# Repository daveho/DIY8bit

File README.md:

# DIY 8-bit computer video series

This repository has files and resources for the DIY 8-bit computer video series I am working on.

My youtube channel: <https://www.youtube.com/@davehohacks>

DIY 8-bit computer playlist: <https://www.youtube.com/playlist?list=PL9zJKV-F2eMyKY6qdesRQP_mAhBCMSw2T>

Some episodes have a specific subdirectory, e.g., `Episode02` for episode 2.

Feedback is welcome: <mailto:david.hovemeyer@gmail.com>.

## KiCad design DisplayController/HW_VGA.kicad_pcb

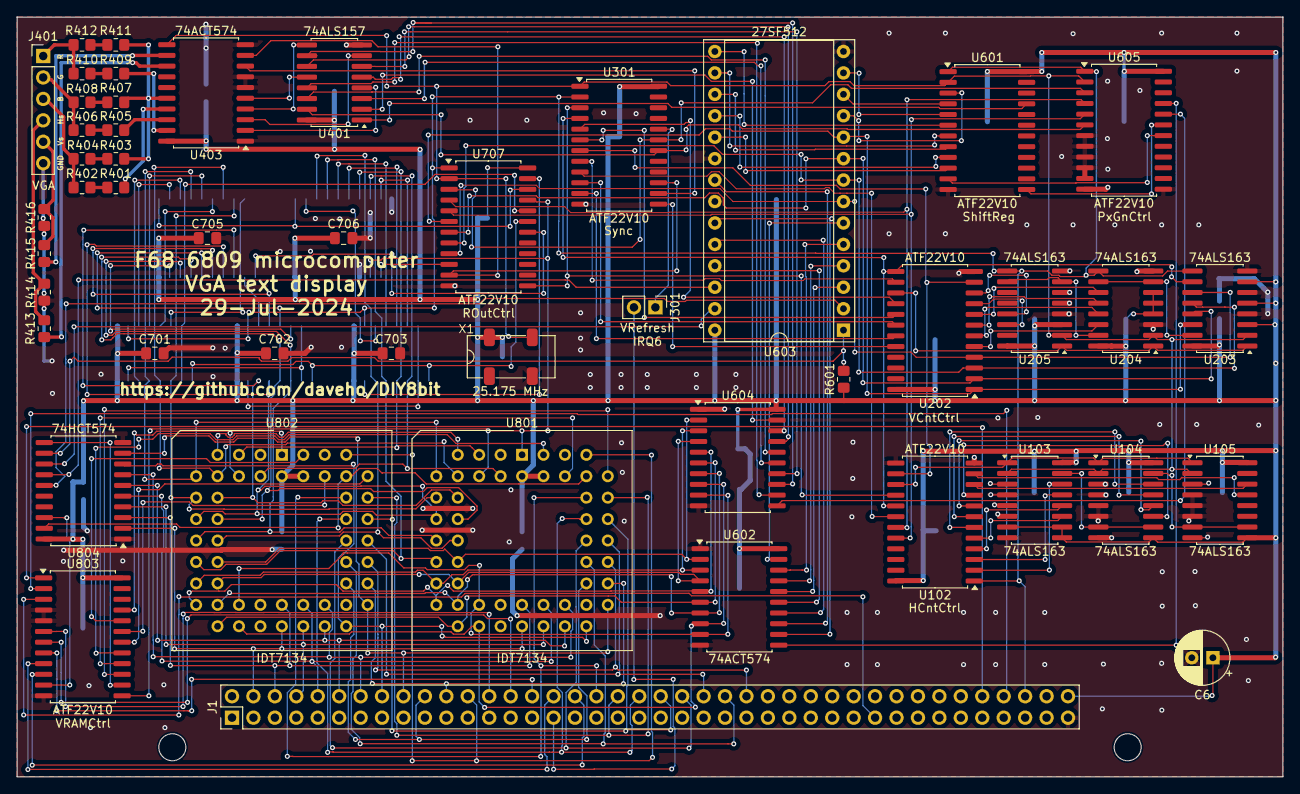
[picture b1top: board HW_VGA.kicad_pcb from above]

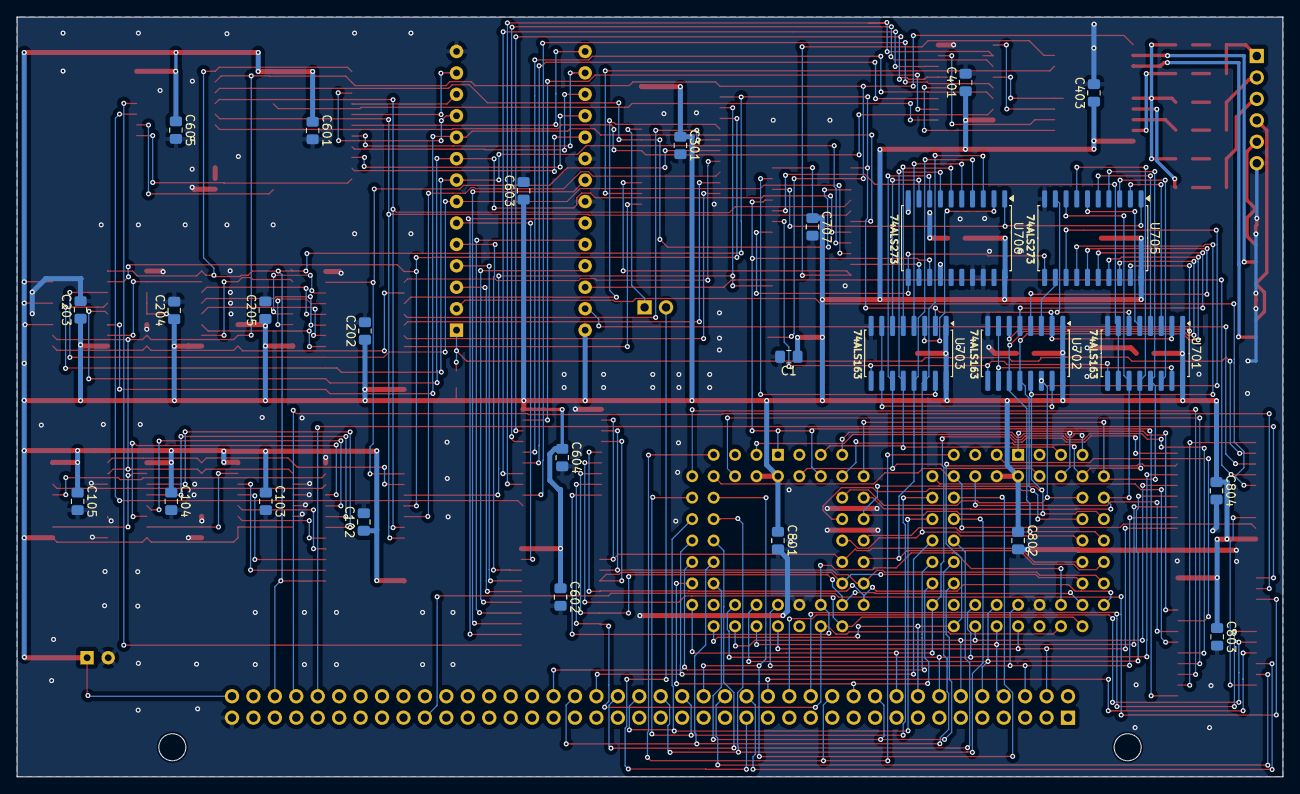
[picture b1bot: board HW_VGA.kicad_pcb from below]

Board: 2 copper layers, 150.0 x 90.0 mm, 75 parts (27 on the bottom side), 181 nets.

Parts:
C1, C102, C103, C104, C105, C202, C203, C204, C205, C301, C401, C403, C601, C602, C603, C604, C605, C701, C702, C703, C705, C706, C707, C801, C802, C803, C804: 100 nF; C_0805_2012Metric_Pad1.18x1.45mm_HandSolder
C6: 22μF; CP_Radial_D6.3mm_P2.50mm
J1: Conn_02x40_Odd_Even; PinHeader_2x40_P2.54mm_Vertical
J301: Conn_01x02; PinHeader_1x02_P2.54mm_Vertical
J401: Conn_01x06; PinHeader_1x06_P2.54mm_Vertical
R401, R405, R409: 620; R_0805_2012Metric_Pad1.20x1.40mm_HandSolder
R402, R406, R410: 75; R_0805_2012Metric_Pad1.20x1.40mm_HandSolder
R403, R407, R411: 1K; R_0805_2012Metric_Pad1.20x1.40mm_HandSolder
R404, R408, R412: 390; R_0805_2012Metric_Pad1.20x1.40mm_HandSolder
R413, R415: 2K; R_0805_2012Metric_Pad1.20x1.40mm_HandSolder
R414, R416: 3K; R_0805_2012Metric_Pad1.20x1.40mm_HandSolder
R601: 4k7; R_0805_2012Metric_Pad1.20x1.40mm_HandSolder
U102, U202, U301, U601, U605, U707, U803: ATF22V10; SOIC-24W_7.5x15.4mm_P1.27mm
U103, U104, U105, U203, U204, U205, U701, U702, U703: 74ALS163; SOIC-16W_5.3x10.2mm_P1.27mm
U401: 74ALS157; SOIC-16W_5.3x10.2mm_P1.27mm
U403, U602, U604: 74ACT574; SOIC-20W_7.5x12.8mm_P1.27mm
U603: 27SF512; DIP-28_W15.24mm_Socket
U705, U706: 74ALS273; SOIC-20W_7.5x12.8mm_P1.27mm
U801, U802: IDT7134; PLCC-52_THT-Socket
U804: 74HCT574; SOIC-20W_7.5x12.8mm_P1.27mm
X1: 25.175 MHz; SG-636P

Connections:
/-HostRMEM: J1.72, U803.1 (I0/CLK)
/-HostWMEM: J1.74, U803.2 (I1)
/-RST: J1.76, U102.1 (I0/CLK), U203.9 (~PE), U204.9 (~PE), U205.9 (~PE), U301.2 (I1), U601.1 (I0/CLK), U605.1 (I0/CLK), U701.2 (CP), U702.2 (CP), U703.2 (CP), U707.1 (I0/CLK)
/-VIS: U301.18 (I/O16), U401.15 (E), U605.6 (I5)
/BGBlue: U401.11 (I0c), U604.17 (Q2)
/BGGreen: U401.5 (I0b), U604.18 (Q1)
/BGIntens: U401.14 (I0d), U604.16 (Q3)
/BGRed: U401.2 (I0a), U604.19 (Q0)
/CLK: U103.2 (CP), U104.2 (CP), U105.2 (CP), U203.2 (CP), U204.2 (CP), U205.2 (CP), U301.1 (I0/CLK), U403.11 (Cp), U601.2 (I1), U605.2 (I1), U707.2 (I1), X1.3 (OUT)
/FGBlue: U401.10 (I1c), U604.13 (Q6)
/FGGreen: U401.6 (I1b), U604.14 (Q5)
/FGIntens: U401.13 (I1d), U604.12 (Q7)
/FGRed: U401.3 (I1a), U604.15 (Q4)
/FontA12: U603.2 (A12), U804.15 (Q4)
/FontA13: U603.26 (A13), U804.14 (Q5)
/FontA14: U603.27 (A14), U804.13 (Q6)
/FontA15: R601.2, U603.1 (A15), U804.12 (Q7)
/HBeginActive: U102.19 (I/O17), U605.4 (I3), U707.4 (I3)
/HBeginPulse: U102.16 (I/O14), U301.3 (I2), U707.13 (I11)
/HCOUNT_END: U102.14 (I/O12), U202.11 (I10), U301.7 (I6)
/HCount/-HCOUNT_CLR: U102.15 (I/O13), U103.1 (~MR), U104.1 (~MR), U105.1 (~MR)
/HCount/HC0: U102.2 (I1), U103.14 (Q0)
/HCount/HC1: U102.3 (I2), U103.13 (Q1)
/HCount/HC2: U102.4 (I3), U103.12 (Q2)
/HCount/HC3: U102.5 (I4), U103.11 (Q3)
/HCount/HC4: U102.6 (I5), U104.14 (Q0)
/HCount/HC5: U102.7 (I6), U104.13 (Q1)
/HCount/HC6: U102.8 (I7), U104.12 (Q2)
/HCount/HC7: U102.9 (I8), U104.11 (Q3)
/HCount/HC8: U102.10 (I9), U105.14 (Q0)
/HCount/HC9: U102.11 (I10), U105.13 (Q1)
/HEndActive: U102.20 (I/O18), U605.5 (I4), U707.5 (I4)
/HEndPulse: U102.17 (I/O15), U202.13 (I11), U203.10 (CET), U301.4 (I3)
/HSync: U301.14 (I/O12), U403.8 (D6)
/HVisEnd: U102.18 (I/O16), U301.9 (I8)
/HostA0: J1.36, U801.45 (A0R), U802.45 (A0R)
/HostA1: J1.38, U801.44 (A1R), U802.44 (A1R)
/HostA2: J1.40, U801.43 (A2R), U802.43 (A2R)
/HostA3: J1.42, U801.42 (A3R), U802.42 (A3R)
/HostA4: J1.44, U801.41 (A4R), U802.41 (A4R)
/HostA5: J1.46, U801.40 (A5R), U802.40 (A5R)
/HostA6: J1.48, U801.39 (A6R), U802.39 (A6R)
/HostA7: J1.50, U801.38 (A7R), U802.38 (A7R)
/HostA8: J1.20, U801.37 (A8R), U802.37 (A8R)
/HostA9: J1.22, U801.36 (A9R), U802.36 (A9R)
/HostA10: J1.24, U801.47 (A10R), U802.47 (A10R)
/HostA11: J1.26, U803.6 (I5)
/HostA12: J1.28, U803.7 (I6)
/HostA13: J1.30, U803.8 (I7)
/HostA14: J1.32, U803.9 (I8)
/HostA15: J1.34, U803.10 (I9)
/HostD0: J1.4, U801.27 (IOR0), U802.27 (IOR0), U804.2 (D0)
/HostD1: J1.6, U801.28 (IOR1), U802.28 (IOR1), U804.3 (D1)
/HostD2: J1.8, U801.29 (IOR2), U802.29 (IOR2), U804.4 (D2)
/HostD3: J1.10, U801.30 (IOR3), U802.30 (IOR3), U804.5 (D3)
/HostD4: J1.12, U801.31 (IOR4), U802.31 (IOR4), U804.6 (D4)
/HostD5: J1.14, U801.32 (IOR5), U802.32 (IOR5), U804.7 (D5)
/HostD6: J1.16, U801.33 (IOR6), U802.33 (IOR6), U804.8 (D6)
/HostD7: J1.18, U801.34 (IOR7), U802.34 (IOR7), U804.9 (D7)
/IRQ6: J1.31, J301.2
/Output/Blue: R401.2, U403.17 (Q2)
/Output/Bout: J401.3, R402.1, R404.2
/Output/Gout: J401.2, R406.1, R408.2
/Output/Green: R405.2, U403.18 (Q1)
/Output/HSyncOut: J401.4, R413.2, R414.1
/Output/Intense: R403.1, R407.1, R411.1, U403.16 (Q3)
/Output/Red: R409.2, U403.19 (Q0)
/Output/Rout: J401.1, R410.1, R412.2
/Output/VSyncOut: J401.5, R415.2, R416.1
/Pixel: U401.1 (S), U601.21 (I/O19)
/Pixgen/-SRLoad: U601.11 (I10), U605.18 (I/O16)
/Pixgen/-SRShift: U601.13 (I11), U605.19 (I/O17)
/Pixgen/CD0: U601.3 (I2), U603.11 (D0)
/Pixgen/CD1: U601.4 (I3), U603.12 (D1)
/Pixgen/CD2: U601.5 (I4), U603.13 (D2)
/Pixgen/CD3: U601.6 (I5), U603.15 (D3)
/Pixgen/CD4: U601.7 (I6), U603.16 (D4)
/Pixgen/CD5: U601.8 (I7), U603.17 (D5)
/Pixgen/CD6: U601.9 (I8), U603.18 (D6)
/Pixgen/CD7: U601.10 (I9), U603.19 (D7)
/Pixgen/CRA4: U602.19 (Q0), U603.6 (A4)
/Pixgen/CRA5: U602.18 (Q1), U603.5 (A5)
/Pixgen/CRA6: U602.17 (Q2), U603.4 (A6)
/Pixgen/CRA7: U602.16 (Q3), U603.3 (A7)
/Pixgen/CRA8: U602.15 (Q4), U603.25 (A8)
/Pixgen/CRA9: U602.14 (Q5), U603.24 (A9)
/Pixgen/CRA10: U602.13 (Q6), U603.21 (A10)
/Pixgen/CRA11: U602.12 (Q7), U603.23 (A11)
/Pixgen/LoadAttrCP: U604.11 (Cp), U605.20 (I/O18)
/Pixgen/LoadCharCP: U602.11 (Cp), U605.21 (I/O19)
/Readout/-LoadReadoutAddr: U701.9 (~PE), U702.9 (~PE), U703.9 (~PE), U707.19 (I/O17)
/Readout/-RowBeginClear: U705.1 (~Mr), U706.1 (~Mr), U707.22 (I/O20)
/Readout/IncrReadoutAddr: U701.7 (CEP), U701.10 (CET), U707.20 (I/O18)
/Readout/ReadoutAddrTCnt: U703.15 (TC), U707.23 (I/O21)
/Readout/RowBeginA0: U701.3 (D0), U705.2 (Q0)
/Readout/RowBeginA1: U701.4 (D1), U705.5 (Q1)
/Readout/RowBeginA2: U701.5 (D2), U705.6 (Q2)
/Readout/RowBeginA3: U701.6 (D3), U705.9 (Q3)
/Readout/RowBeginA4: U702.3 (D0), U705.12 (Q4)
/Readout/RowBeginA5: U702.4 (D1), U705.15 (Q5)
/Readout/RowBeginA6: U702.5 (D2), U705.16 (Q6)
/Readout/RowBeginA7: U702.6 (D3), U705.19 (Q7)
/Readout/RowBeginA8: U703.3 (D0), U706.2 (Q0)
/Readout/RowBeginA9: U703.4 (D1), U706.5 (Q1)
/Readout/RowBeginA10: U703.5 (D2), U706.6 (Q2)
/Readout/RowBeginA11: U703.6 (D3), U706.9 (Q3)
/Readout/RowBeginA12: U706.12 (Q4), U707.10 (I9)
/Readout/UpdateRowBeginCP: U705.11 (Cp), U706.11 (Cp), U707.18 (I/O16)
/ReadoutA0: U701.14 (Q0), U705.3 (D0)
/ReadoutA1: U701.13 (Q1), U705.4 (D1), U801.8 (A1L), U802.8 (A1L)
/ReadoutA2: U701.12 (Q2), U705.7 (D2), U801.9 (A2L), U802.9 (A2L)
/ReadoutA3: U701.11 (Q3), U705.8 (D3), U801.10 (A3L), U802.10 (A3L)
/ReadoutA4: U702.14 (Q0), U705.13 (D4), U801.11 (A4L), U802.11 (A4L)
/ReadoutA5: U702.13 (Q1), U705.14 (D5), U801.12 (A5L), U802.12 (A5L)
/ReadoutA6: U702.12 (Q2), U705.17 (D6), U801.13 (A6L), U802.13 (A6L)
/ReadoutA7: U702.11 (Q3), U705.18 (D7), U801.14 (A7L), U802.14 (A7L)
/ReadoutA8: U703.14 (Q0), U706.3 (D0), U801.15 (A8L), U802.15 (A8L)
/ReadoutA9: U703.13 (Q1), U706.4 (D1), U801.16 (A9L), U802.16 (A9L)
/ReadoutA10: U703.12 (Q2), U706.7 (D2), U801.5 (A10L), U802.5 (A10L)
/ReadoutA11: U703.11 (Q3), U706.8 (D3), U801.4 (A11L), U802.4 (A11L)
/ReadoutA12: U706.13 (D4), U707.21 (I/O19), U801.1 (-CEL), U801.6 (-OEL), U803.13 (I11)
/ReadoutD0: U602.2 (D0), U604.2 (D0), U801.17 (IO0L), U802.17 (IO0L)
/ReadoutD1: U602.3 (D1), U604.3 (D1), U801.18 (IO1L), U802.18 (IO1L)
/ReadoutD2: U602.4 (D2), U604.4 (D2), U801.19 (IO2L), U802.19 (IO2L)
/ReadoutD3: U602.5 (D3), U604.5 (D3), U801.20 (IO3L), U802.20 (IO3L)
/ReadoutD4: U602.6 (D4), U604.6 (D4), U801.21 (IO4L), U802.21 (IO4L)
/ReadoutD5: U602.7 (D5), U604.7 (D5), U801.22 (IO5L), U802.22 (IO5L)
/ReadoutD6: U602.8 (D6), U604.8 (D6), U801.23 (IO6L), U802.23 (IO6L)
/ReadoutD7: U602.9 (D7), U604.9 (D7), U801.24 (IO7L), U802.24 (IO7L)
/VActive: U301.19 (I/O17), U605.3 (I2), U707.3 (I2)
/VBeginPulse: U202.16 (I/O14), U301.5 (I4)
/VC0: U202.1 (I0/CLK), U203.14 (Q0), U603.10 (A0), U707.6 (I5)
/VC1: U202.2 (I1), U203.13 (Q1), U603.9 (A1), U707.7 (I6)
/VC2: U202.3 (I2), U203.12 (Q2), U603.8 (A2), U707.8 (I7)
/VC3: U202.4 (I3), U203.11 (Q3), U603.7 (A3), U707.9 (I8)
/VCOUNT_END: U202.19 (I/O17), U301.11 (I10)
/VCOUNT_ZERO: U202.14 (I/O12), U301.8 (I7)
/VCount/-VCOUNT_CLR: U202.15 (I/O13), U203.1 (~MR), U204.1 (~MR), U205.1 (~MR)
/VCount/VC4: U202.5 (I4), U204.14 (Q0)
/VCount/VC5: U202.6 (I5), U204.13 (Q1)
/VCount/VC6: U202.7 (I6), U204.12 (Q2)
/VCount/VC7: U202.8 (I7), U204.11 (Q3)
/VCount/VC8: U202.9 (I8), U205.14 (Q0)
/VCount/VC9: U202.10 (I9), U205.13 (Q1)
/VEndActive: U202.20 (I/O18), U301.13 (I11)
/VEndPulse: U202.17 (I/O15), U301.6 (I5)
/VRAM/-LowerCE: U801.51 (-CER), U803.17 (I/O15)
/VRAM/-LowerOE: U801.46 (-OER), U803.15 (I/O13)
/VRAM/-ReadoutA12: U802.1 (-CEL), U802.6 (-OEL), U803.21 (I/O19)
/VRAM/-UpperCE: U802.51 (-CER), U803.20 (I/O18)
/VRAM/-UpperOE: U802.46 (-OER), U803.18 (I/O16)
/VRAM/BankA11: U801.48 (A11R), U802.48 (A11R), U804.19 (Q0)
/VRAM/BankA12: U803.11 (I10), U804.18 (Q1)
/VRAM/LowerR/-W: U801.50 (R/-WR), U803.16 (I/O14)
/VRAM/ReadoutA0: U801.7 (A0L), U802.7 (A0L)
/VRAM/UpperR/-W: U802.50 (R/-WR), U803.19 (I/O17)
/VRAM/VBankRegCP: U803.14 (I/O12), U804.11 (Cp)
/VRefresh: J301.1, U301.20 (I/O18)
/VSync: U301.15 (I/O13), U403.9 (D7), U707.11 (I10)
/VVisEnd: U202.18 (I/O16), U301.10 (I9)
/~IODEV7: J1.61, U803.3 (I2)
GND: C1.2, C6.2, C102.2, C103.2, C104.2, C105.2, C202.2, C203.2, C204.2, C205.2, C301.2, C401.2, C403.2, C601.2, C602.2, C603.2, C604.2, C605.2, C701.2, C702.2, C703.2, C705.2, C706.2, C707.2, C801.2, C802.2, C803.2, C804.2, J1.79, J401.6, R414.2, R416.2, U102.12 (GND), U102.13 (I11), U103.3 (D0), U103.4 (D1), U103.5 (D2), U103.6 (D3), U103.8 (GND), U104.3 (D0), U104.4 (D1), U104.5 (D2), U104.6 (D3), U104.8 (GND), U105.3 (D0), U105.4 (D1), U105.5 (D2), U105.6 (D3), U105.8 (GND), U202.12 (GND), U203.4 (D1), U203.6 (D3), U203.8 (GND), U204.3 (D0), U204.8 (GND), U205.4 (D1), U205.5 (D2), U205.6 (D3), U205.8 (GND), U301.12 (GND), U401.8 (GND), U403.1 (OE), U403.6 (D4), U403.7 (D5), U403.10 (GND), U601.12 (GND), U602.1 (OE), U602.10 (GND), U603.14 (GND), U603.20 (-CE), U603.22 (-OE), U604.1 (OE), U604.10 (GND), U605.7 (I6), U605.8 (I7), U605.9 (I8), U605.10 (I9), U605.11 (I10), U605.12 (GND), U605.13 (I11), U701.8 (GND), U702.8 (GND), U703.8 (GND), U705.10 (GND), U706.10 (GND), U706.14 (D5), U706.17 (D6), U706.18 (D7), U707.12 (GND), U801.26 (GND), U802.26 (GND), U803.4 (I3), U803.5 (I4), U803.12 (GND), U804.1 (OE), U804.10 (GND), X1.2 (GND)
unnamed: R401.1, R402.2
unnamed: R403.2, R404.1
unnamed: R405.1, R406.2
unnamed: R407.2, R408.1
unnamed: R409.1, R410.2
unnamed: R411.2, R412.1
unnamed: U103.15 (TC), U104.7 (CEP), U104.10 (CET)
unnamed: U104.15 (TC), U105.7 (CEP), U105.10 (CET)
unnamed: U203.15 (TC), U204.7 (CEP), U204.10 (CET)
unnamed: U204.15 (TC), U205.7 (CEP), U205.10 (CET)
unnamed: U401.4 (Za), U403.2 (D0)
unnamed: U401.7 (Zb), U403.3 (D1)
unnamed: U401.9 (Zc), U403.4 (D2)
unnamed: U401.12 (Zd), U403.5 (D3)
unnamed: R413.1, U403.13 (Q6)
unnamed: R415.1, U403.12 (Q7)
unnamed: U701.15 (TC), U702.7 (CEP), U702.10 (CET)
unnamed: U702.15 (TC), U703.7 (CEP), U703.10 (CET)
VCC: C1.1, C6.1, C102.1, C103.1, C104.1, C105.1, C202.1, C203.1, C204.1, C205.1, C301.1, C401.1, C403.1, C601.1, C602.1, C603.1, C604.1, C605.1, C701.1, C702.1, C703.1, C705.1, C706.1, C707.1, C801.1, C802.1, C803.1, C804.1, J1.80, R601.1, U102.24 (VCC), U103.7 (CEP), U103.9 (~PE), U103.10 (CET), U103.16 (VCC), U104.9 (~PE), U104.16 (VCC), U105.9 (~PE), U105.16 (VCC), U202.24 (VCC), U203.3 (D0), U203.5 (D2), U203.7 (CEP), U203.16 (VCC), U204.4 (D1), U204.5 (D2), U204.6 (D3), U204.16 (VCC), U205.3 (D0), U205.16 (VCC), U301.24 (VCC), U401.16 (VCC), U403.20 (VCC), U601.24 (VCC), U602.20 (VCC), U603.28 (VCC), U604.20 (VCC), U605.24 (VCC), U701.1 (~MR), U701.16 (VCC), U702.1 (~MR), U702.16 (VCC), U703.1 (~MR), U703.16 (VCC), U705.20 (VCC), U706.20 (VCC), U707.24 (VCC), U801.2 (R/-WL), U801.52 (VCC), U802.2 (R/-WL), U802.52 (VCC), U803.24 (VCC), U804.20 (VCC), X1.4 (VCC)

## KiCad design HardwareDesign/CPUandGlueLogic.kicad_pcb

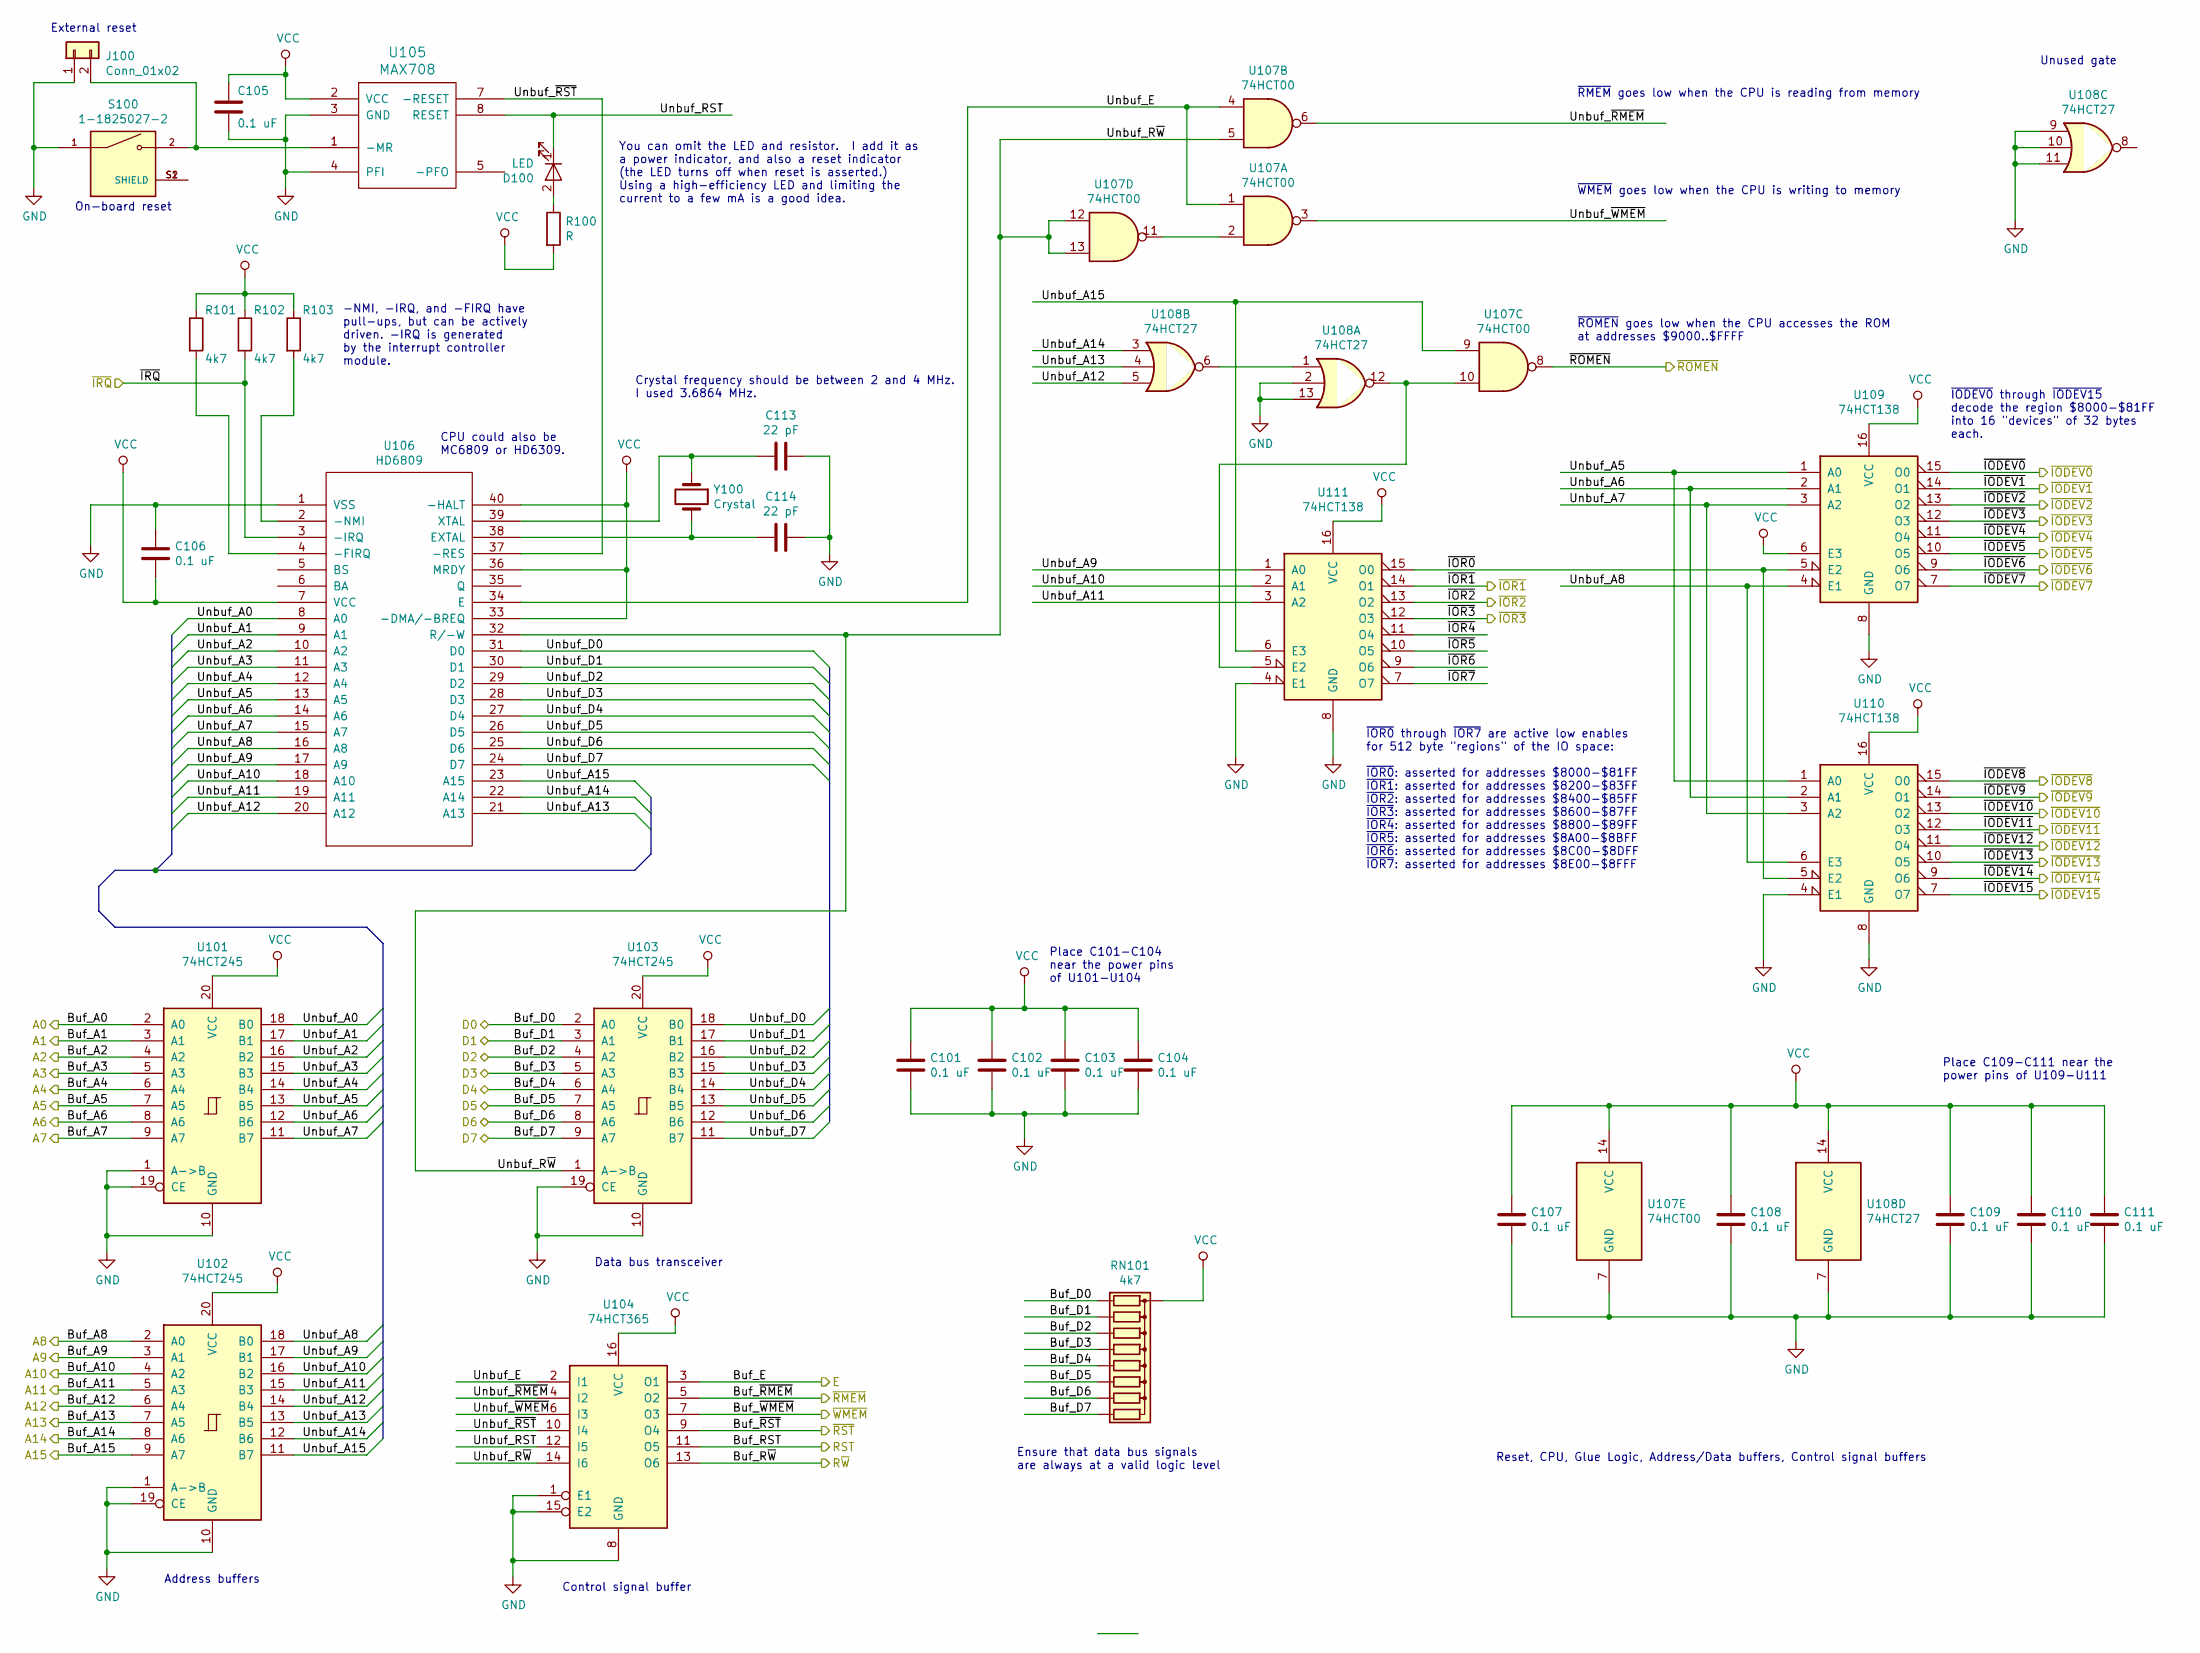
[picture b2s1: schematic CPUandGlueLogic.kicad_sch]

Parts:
C101, C102, C103, C104, C105, C106, C107, C108, C109, C110, C111: 0.1 uF; C_Disc_D5.0mm_W2.5mm_P2.50mm
C113, C114: 22 pF; C_Disc_D3.8mm_W2.6mm_P2.50mm
D100: LED; LED_D5.0mm
J100: Conn_01x02; PinHeader_1x02_P2.54mm_Vertical
R100: R; R_Axial_DIN0204_L3.6mm_D1.6mm_P7.62mm_Horizontal
R101, R102, R103: 4k7; R_Axial_DIN0204_L3.6mm_D1.6mm_P7.62mm_Horizontal
RN101: 4k7; R_Array_SIP9
S100: 1-1825027-2; SW_1-1825027-2
U101, U102, U103: 74HCT245; DIP-20_W7.62mm_Socket
U104: 74HCT365; DIP-16_W7.62mm_Socket
U105: MAX708; DIP-8_W7.62mm_Socket
U106: HD6809; DIP-40_W15.24mm_Socket
U107: 74HCT00; DIP-14_W7.62mm_Socket
U108: 74HCT27; DIP-14_W7.62mm_Socket
U109, U110, U111: 74HCT138; DIP-16_W7.62mm_Socket
Y100: Crystal; Crystal_HC18-U_Vertical

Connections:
/A0: U101.2 (A0); also elsewhere on the board
/A1: U101.3 (A1); also elsewhere on the board
/A2: U101.4 (A2); also elsewhere on the board
/A3: U101.5 (A3); also elsewhere on the board
/A4: U101.6 (A4); also elsewhere on the board
/A5: U101.7 (A5); also elsewhere on the board
/A6: U101.8 (A6); also elsewhere on the board
/A7: U101.9 (A7); also elsewhere on the board
/A8: U102.2 (A0); also elsewhere on the board
/A9: U102.3 (A1); also elsewhere on the board
/A10: U102.4 (A2); also elsewhere on the board
/A11: U102.5 (A3); also elsewhere on the board
/A12: U102.6 (A4); also elsewhere on the board
/A13: U102.7 (A5); also elsewhere on the board
/A14: U102.8 (A6); also elsewhere on the board
/A15: U102.9 (A7); also elsewhere on the board
/CPUandGlueLogic/Unbuf_A0: U101.18 (B0), U106.8 (A0)
/CPUandGlueLogic/Unbuf_A1: U101.17 (B1), U106.9 (A1)
/CPUandGlueLogic/Unbuf_A2: U101.16 (B2), U106.10 (A2)
/CPUandGlueLogic/Unbuf_A3: U101.15 (B3), U106.11 (A3)
/CPUandGlueLogic/Unbuf_A4: U101.14 (B4), U106.12 (A4)
/CPUandGlueLogic/Unbuf_A5: U101.13 (B5), U106.13 (A5), U109.1 (A0), U110.1 (A0)
/CPUandGlueLogic/Unbuf_A6: U101.12 (B6), U106.14 (A6), U109.2 (A1), U110.2 (A1)
/CPUandGlueLogic/Unbuf_A7: U101.11 (B7), U106.15 (A7), U109.3 (A2), U110.3 (A2)
/CPUandGlueLogic/Unbuf_A8: U102.18 (B0), U106.16 (A8), U109.4 (E1), U110.6 (E3)
/CPUandGlueLogic/Unbuf_A9: U102.17 (B1), U106.17 (A9), U111.1 (A0)
/CPUandGlueLogic/Unbuf_A10: U102.16 (B2), U106.18 (A10), U111.2 (A1)
/CPUandGlueLogic/Unbuf_A11: U102.15 (B3), U106.19 (A11), U111.3 (A2)
/CPUandGlueLogic/Unbuf_A12: U102.14 (B4), U106.20 (A12), U108.5
/CPUandGlueLogic/Unbuf_A13: U102.13 (B5), U106.21 (A13), U108.4
/CPUandGlueLogic/Unbuf_A14: U102.12 (B6), U106.22 (A14), U108.3
/CPUandGlueLogic/Unbuf_A15: U102.11 (B7), U106.23 (A15), U107.9, U111.6 (E3)
/CPUandGlueLogic/Unbuf_D0: U103.18 (B0), U106.31 (D0)
/CPUandGlueLogic/Unbuf_D1: U103.17 (B1), U106.30 (D1)
/CPUandGlueLogic/Unbuf_D2: U103.16 (B2), U106.29 (D2)
/CPUandGlueLogic/Unbuf_D3: U103.15 (B3), U106.28 (D3)
/CPUandGlueLogic/Unbuf_D4: U103.14 (B4), U106.27 (D4)
/CPUandGlueLogic/Unbuf_D5: U103.13 (B5), U106.26 (D5)
/CPUandGlueLogic/Unbuf_D6: U103.12 (B6), U106.25 (D6)
/CPUandGlueLogic/Unbuf_D7: U103.11 (B7), U106.24 (D7)
/CPUandGlueLogic/Unbuf_E: U104.2 (I1), U106.34 (E), U107.1, U107.4
/CPUandGlueLogic/Unbuf_RST: D100.1 (K), U104.12 (I5), U105.8 (RESET)
/CPUandGlueLogic/Unbuf_R~W~: U103.1 (A->B), U104.14 (I6), U106.32 (R/-W), U107.5, U107.12, U107.13
/CPUandGlueLogic/Unbuf_~RMEM~: U104.4 (I2), U107.6
/CPUandGlueLogic/Unbuf_~RST~: U104.10 (I4), U105.7 (-RESET), U106.37 (-RES)
/CPUandGlueLogic/Unbuf_~WMEM~: U104.6 (I3), U107.3
/CPUandGlueLogic/~IOR0~: U109.5 (E2), U110.5 (E2), U111.15 (O0)
/CPUandGlueLogic/~IOR4~: U111.11 (O4)
/CPUandGlueLogic/~IOR5~: U111.10 (O5)
/CPUandGlueLogic/~IOR6~: U111.9 (O6)
/CPUandGlueLogic/~IOR7~: U111.7 (O7)
/D0: RN101.2 (R1), U103.2 (A0); also elsewhere on the board
/D1: RN101.3 (R2), U103.3 (A1); also elsewhere on the board
/D2: RN101.4 (R3), U103.4 (A2); also elsewhere on the board
/D3: RN101.5 (R4), U103.5 (A3); also elsewhere on the board
/D4: RN101.6 (R5), U103.6 (A4); also elsewhere on the board
/D5: RN101.7 (R6), U103.7 (A5); also elsewhere on the board
/D6: RN101.8 (R7), U103.8 (A6); also elsewhere on the board
/D7: RN101.9 (R8), U103.9 (A7); also elsewhere on the board
/E: U104.3 (O1); also elsewhere on the board
/RST: U104.11 (O5); also elsewhere on the board
/R~W~: U104.13 (O6); also elsewhere on the board
/~IODEV0: U109.15 (O0); also elsewhere on the board
/~IODEV1: U109.14 (O1); also elsewhere on the board
/~IODEV2: U109.13 (O2); also elsewhere on the board
/~IODEV3: U109.12 (O3); also elsewhere on the board
/~IODEV4: U109.11 (O4); also elsewhere on the board
/~IODEV5: U109.10 (O5); also elsewhere on the board
/~IODEV6: U109.9 (O6); also elsewhere on the board
/~IODEV7: U109.7 (O7); also elsewhere on the board
/~IODEV8: U110.15 (O0); also elsewhere on the board
/~IODEV9: U110.14 (O1); also elsewhere on the board
/~IODEV10: U110.13 (O2); also elsewhere on the board
/~IODEV11: U110.12 (O3); also elsewhere on the board
/~IODEV12: U110.11 (O4); also elsewhere on the board
/~IODEV13: U110.10 (O5); also elsewhere on the board
/~IODEV14: U110.9 (O6); also elsewhere on the board
/~IODEV15: U110.7 (O7); also elsewhere on the board
/~IOR1~: U111.14 (O1); also elsewhere on the board
/~IOR2~: U111.13 (O2); also elsewhere on the board
/~IOR3~: U111.12 (O3); also elsewhere on the board
/~IRQ: R102.2, U106.3 (-IRQ); also elsewhere on the board
/~RMEM~: U104.5 (O2); also elsewhere on the board
/~ROMEN~: U107.8; also elsewhere on the board
/~RST~: U104.9 (O4); also elsewhere on the board
/~WMEM~: U104.7 (O3); also elsewhere on the board
GND: C101.2, C102.2, C103.2, C104.2, C105.2, C106.1, C107.2, C108.2, C109.2, C110.2, C111.2, C113.1, C114.1, J100.1, S100.1, U101.1 (A->B), U101.10 (GND), U101.19 (CE), U102.1 (A->B), U102.10 (GND), U102.19 (CE), U103.10 (GND), U103.19 (CE), U104.1 (E1), U104.8 (GND), U104.15 (E2), U105.3 (GND), U105.4 (PFI), U106.1 (VSS), U107.7 (GND), U108.2, U108.7 (GND), U108.9, U108.10, U108.11, U108.13, U109.8 (GND), U110.4 (E1), U110.8 (GND), U111.4 (E1), U111.8 (GND); also elsewhere on the board
unnamed: C113.2, U106.39 (XTAL), Y100.1
unnamed: C114.2, U106.38 (EXTAL), Y100.2
unnamed: D100.2 (A), R100.1
unnamed: J100.2, S100.2, U105.1 (-MR)
unnamed: R101.2, U106.4 (-FIRQ)
unnamed: R103.2, U106.2 (-NMI)
unnamed: S100.S1 (SHIELD), S100.S2 (SHIELD)
unnamed: U107.10, U108.12, U111.5 (E2)
unnamed: U107.2, U107.11
unnamed: U108.1, U108.6
VCC: C101.1, C102.1, C103.1, C104.1, C105.1, C106.2, C107.1, C108.1, C109.1, C110.1, C111.1, R100.2, R101.1, R102.1, R103.1, RN101.1 (common), U101.20 (VCC), U102.20 (VCC), U103.20 (VCC), U104.16 (VCC), U105.2 (VCC), U106.7 (VCC), U106.33 (-DMA/-BREQ), U106.36 (MRDY), U106.40 (-HALT), U107.14 (VCC), U108.14 (VCC), U109.6 (E3), U109.16 (VCC), U110.16 (VCC), U111.16 (VCC); also elsewhere on the board

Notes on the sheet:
~{WMEM} goes low when the CPU is writing to memory
Place C109-C111 near the power pins of U109-U111
External reset
-NMI, -IRQ, and -FIRQ have pull-ups, but can be actively driven. -IRQ is generated by the interrupt controller module.
Reset, CPU, Glue Logic, Address/Data buffers, Control signal buffers
You can omit the LED and resistor. I add it as a power indicator, and also a reset indicator (the LED turns off when reset is asserted.) Using a high-efficiency LED and limiting the current to a few mA is a good idea.
On-board reset
Crystal frequency should be between 2 and 4 MHz. I used 3.6864 MHz.
Control signal buffer
~{IOR0} through ~{IOR7} are active low enables for 512 byte "regions" of the IO space: ~{IOR0}: asserted for addresses $8000-$81FF ~{IOR1}: asserted for addresses $8200-$83FF ~{IOR2}: asserted for addresses $8400-$85FF ~{IOR3}: asserted for addresses $8600-$87FF ~{IOR4}: asserted for addresses $880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
Address buffers
CPU could also be MC6809 or HD6309.
~{IODEV0} through ~{IODEV15} decode the region $8000-$81FF into 16 "devices" of 32 bytes each.
~{ROMEN} goes low when the CPU accesses the ROM at addresses $9000..$FFFF
Unused gate
~{RMEM} goes low when the CPU is reading from memory
Ensure that data bus signals are always at a valid logic level
Place C101-C104 near the power pins of U101-U104
Data bus transceiver

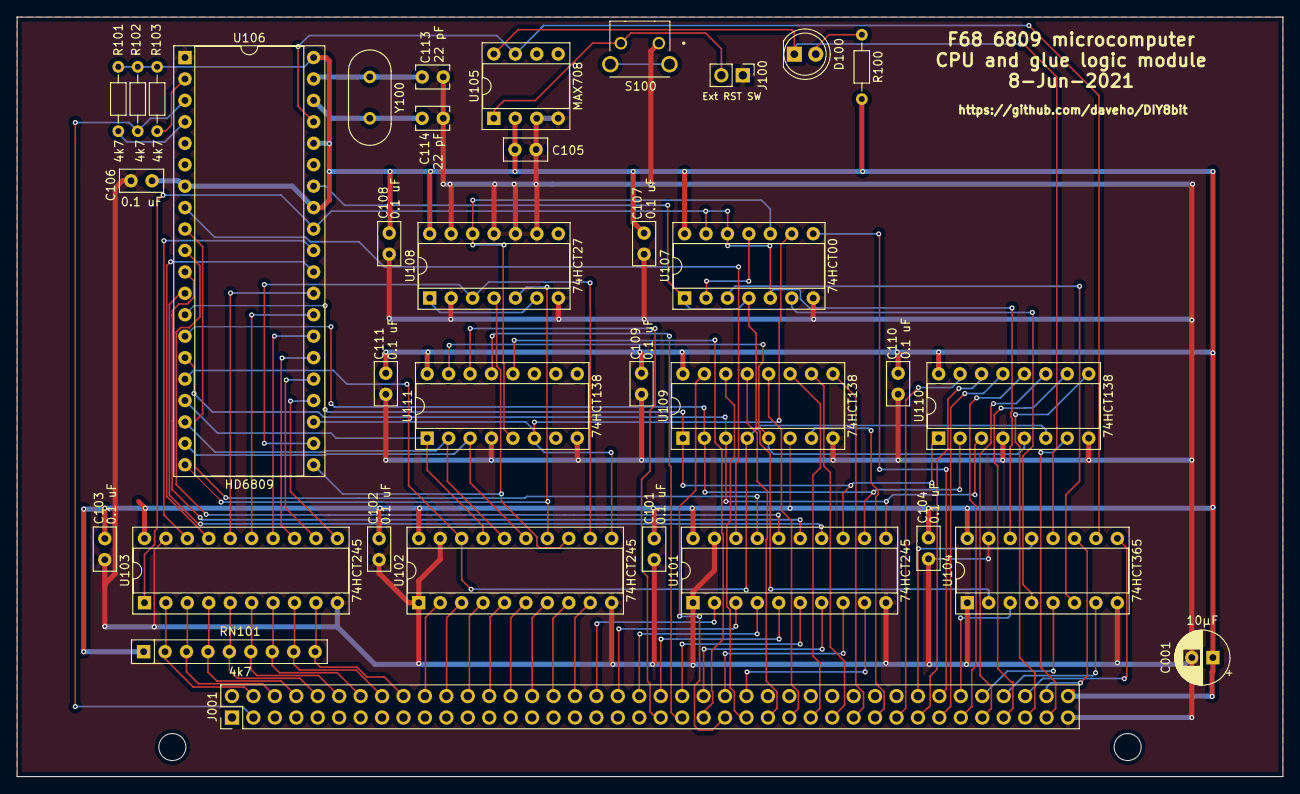
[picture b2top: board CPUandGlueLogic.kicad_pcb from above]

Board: 2 copper layers, 150.0 x 90.0 mm, 35 parts (0 on the bottom side), 94 nets.

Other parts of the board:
C001: 10μF; CP_Radial_D6.3mm_P2.50mm
J001: Conn_02x40_Odd_Even; PinHeader_2x40_P2.54mm_Vertical

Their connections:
/A0: J001.36; also elsewhere on the board
/A1: J001.38; also elsewhere on the board
/A2: J001.40; also elsewhere on the board
/A3: J001.42; also elsewhere on the board
/A4: J001.44; also elsewhere on the board
/A5: J001.46; also elsewhere on the board
/A6: J001.48; also elsewhere on the board
/A7: J001.50; also elsewhere on the board
/A8: J001.20; also elsewhere on the board
/A9: J001.22; also elsewhere on the board
/A10: J001.24; also elsewhere on the board
/A11: J001.26; also elsewhere on the board
/A12: J001.28; also elsewhere on the board
/A13: J001.30; also elsewhere on the board
/A14: J001.32; also elsewhere on the board
/A15: J001.34; also elsewhere on the board
/D0: J001.4; also elsewhere on the board
/D1: J001.6; also elsewhere on the board
/D2: J001.8; also elsewhere on the board
/D3: J001.10; also elsewhere on the board
/D4: J001.12; also elsewhere on the board
/D5: J001.14; also elsewhere on the board
/D6: J001.16; also elsewhere on the board
/D7: J001.18; also elsewhere on the board
/E: J001.70; also elsewhere on the board
/RST: J001.78; also elsewhere on the board
/R~W~: J001.66; also elsewhere on the board
/~IODEV0: J001.47; also elsewhere on the board
/~IODEV1: J001.49; also elsewhere on the board
/~IODEV2: J001.51; also elsewhere on the board
/~IODEV3: J001.53; also elsewhere on the board
/~IODEV4: J001.55; also elsewhere on the board
/~IODEV5: J001.57; also elsewhere on the board
/~IODEV6: J001.59; also elsewhere on the board
/~IODEV7: J001.61; also elsewhere on the board
/~IODEV8: J001.63; also elsewhere on the board
/~IODEV9: J001.65; also elsewhere on the board
/~IODEV10: J001.67; also elsewhere on the board
/~IODEV11: J001.69; also elsewhere on the board
/~IODEV12: J001.71; also elsewhere on the board
/~IODEV13: J001.73; also elsewhere on the board
/~IODEV14: J001.75; also elsewhere on the board
/~IODEV15: J001.77; also elsewhere on the board
/~IOR1~: J001.41; also elsewhere on the board
/~IOR2~: J001.43; also elsewhere on the board
/~IOR3~: J001.45; also elsewhere on the board
/~IRQ: J001.3; also elsewhere on the board
/~RMEM~: J001.72; also elsewhere on the board
/~ROMEN~: J001.68; also elsewhere on the board
/~RST~: J001.76; also elsewhere on the board
/~WMEM~: J001.74; also elsewhere on the board
GND: C001.2, J001.79; also elsewhere on the board
VCC: C001.1, J001.80; also elsewhere on the board
